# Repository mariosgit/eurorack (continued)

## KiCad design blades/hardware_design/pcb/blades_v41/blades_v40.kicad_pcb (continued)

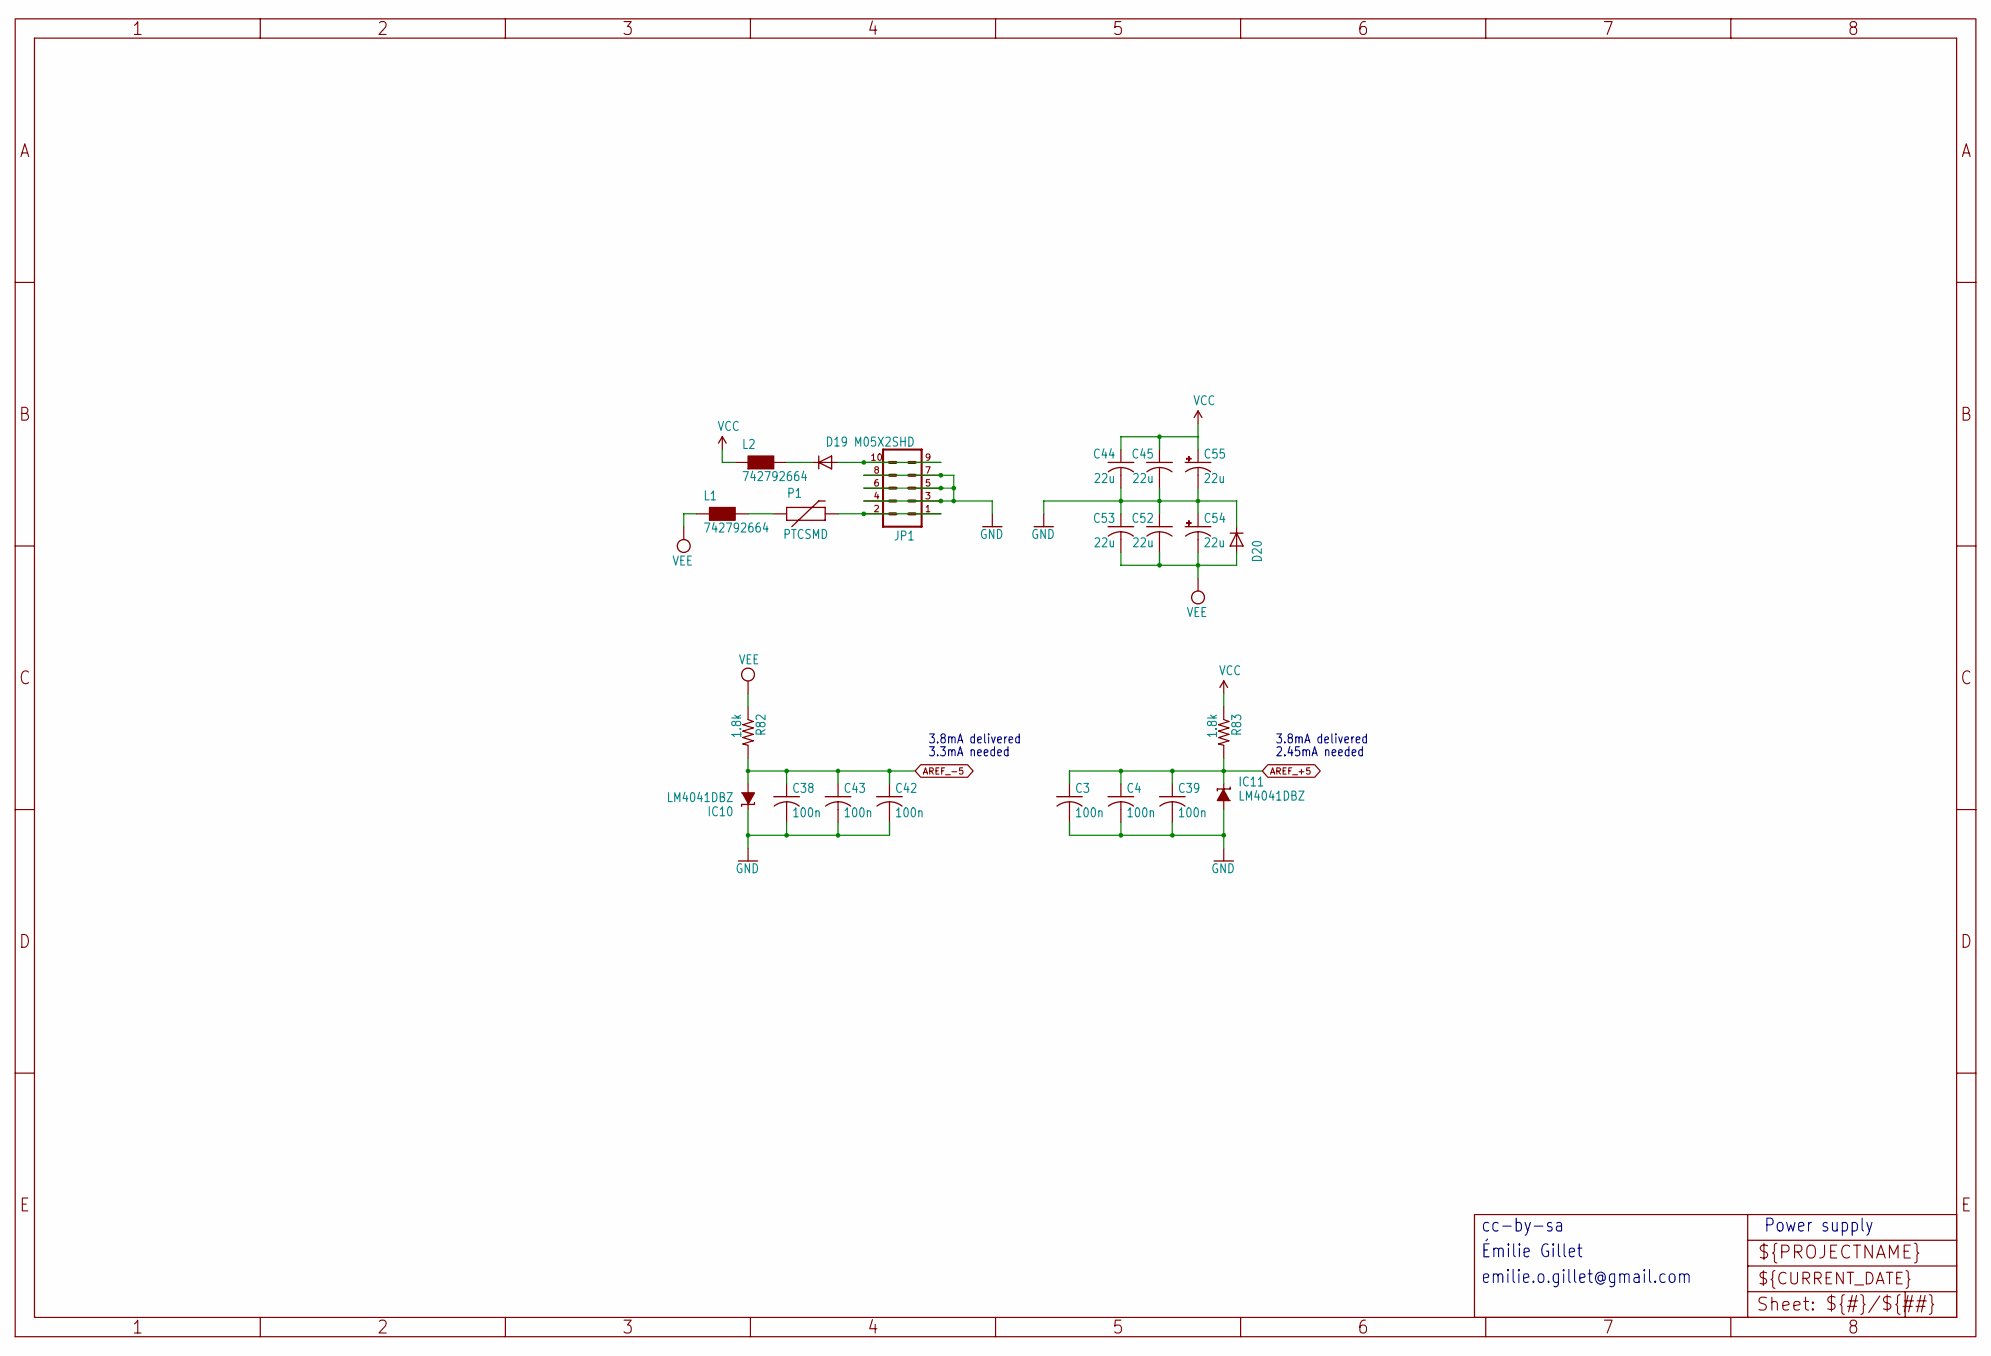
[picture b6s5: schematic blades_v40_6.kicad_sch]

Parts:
C3, C4, C38, C39, C42, C43: 100n; C0402
C44, C45, C52, C53: 22u; C1206
C54, C55: 22u; PANASONIC_B
D19, D20: 1N5819HW; SOD123
IC10, IC11: LM4041DBZ; DBZ_R-PDSO-G3
JP1: M05X2SHD; 2X5-SHROUDED
L1, L2: 742792664; 0603
P1: PTCSMD; PTC-1206
R82, R83: 1.8k; R0402

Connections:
AREF_+5: C3.1, C4.1, C39.1, IC11.1 (C), R83.2; also elsewhere on the board
AREF_-5: C38.1, C42.1, C43.1, IC10.2 (A), R82.2; also elsewhere on the board
GND: C3.2, C4.2, C38.2, C39.2, C42.2, C43.2, C44.2, C45.2, C52.1, C53.1, C54.+, C55.-, D20.C, IC10.1 (C), IC11.2 (A), JP1.3, JP1.4, JP1.5, JP1.6, JP1.7, JP1.8; also elsewhere on the board
unnamed: D19.A, JP1.9, JP1.10
unnamed: D19.C, L2.2
unnamed: JP1.1, JP1.2, P1.2
unnamed: L1.2, P1.1
VCC: C44.1, C45.1, C55.+, L2.1, R83.1; also elsewhere on the board
VEE: C52.2, C53.2, C54.-, D20.A, L1.1, R82.1; also elsewhere on the board

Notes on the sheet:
2.45mA needed
cc-by-sa
emilie.o.gillet@gmail.com
Émilie Gillet
3.8mA delivered
Power supply
3.3mA needed

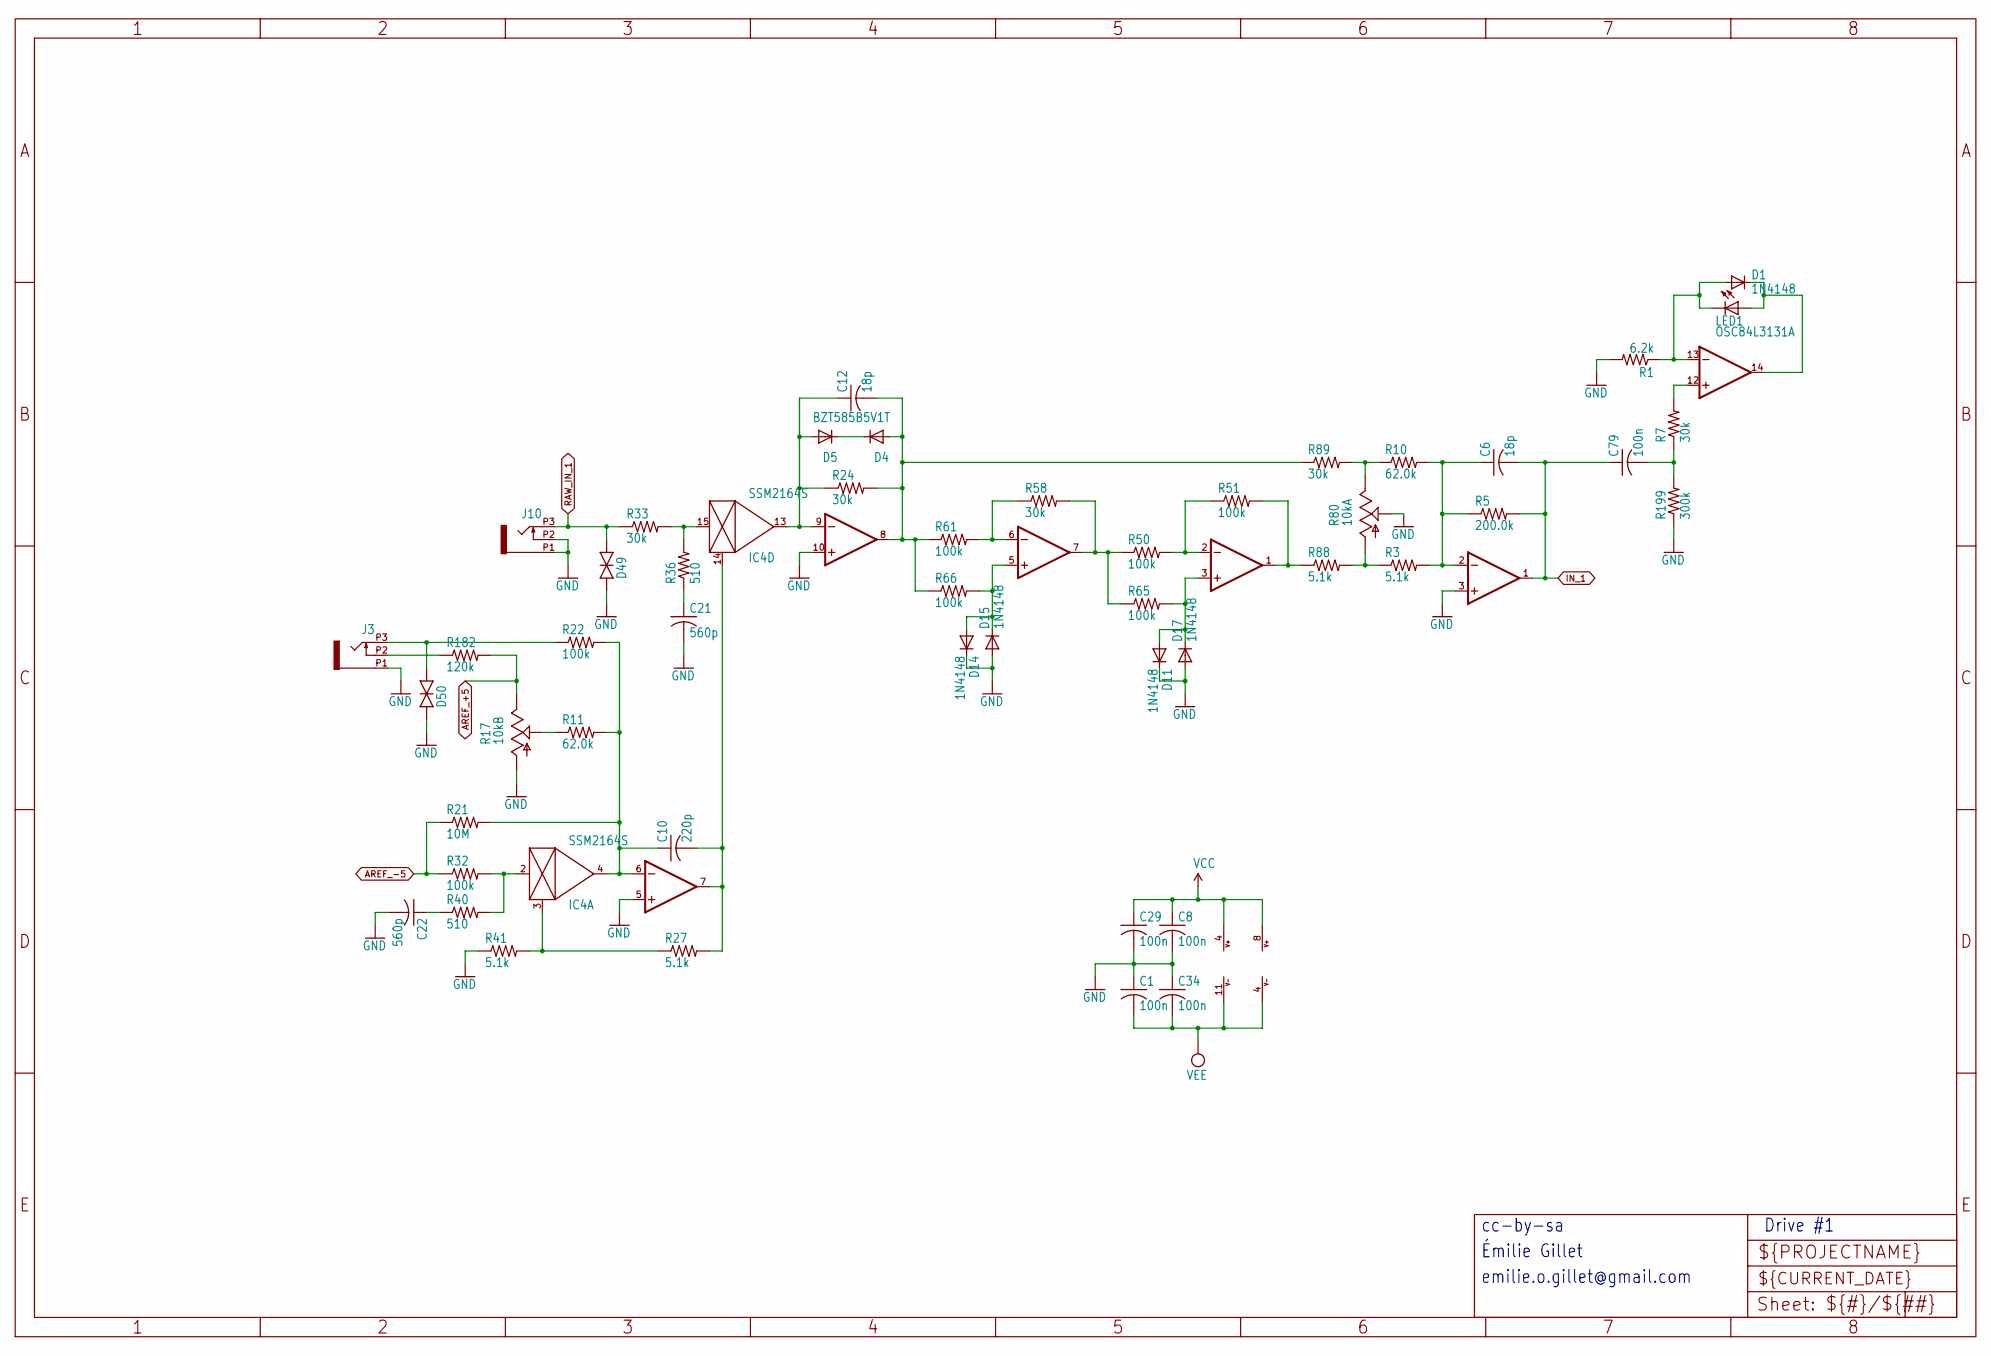
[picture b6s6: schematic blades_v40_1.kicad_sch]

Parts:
C1, C8, C29, C34, C79: 100n; C0402
C6, C12: 18p; C0402
C10: 220p; C0402
C21, C22: 560p; C0402
D1, D11, D14, D15, D17: 1N4148; SOD523
D4, D5: BZT585B5V1T; SOD523
D49, D50: TVS; 0603
IC2: OPA1679PW; TSSOP14_065
IC4: SSM2164S; SOIC16N
IC6: OPA1678DGK; VSSOP8
J3, J10: PJ301_THONKICONNTME; WQP_PJ_301M_TME
LED1: OSC84L3131A; LED3MM
R1: 6.2k; R0402
R3, R27, R41, R88: 5.1k; R0402
R5: 200.0k; R0402
R7, R24, R33, R58, R89: 30k; R0402
R10, R11: 62.0k; R0402
R17: 10kB; ALPS_POT_VERTICAL_PS
R21: 10M; R0402
R22, R32, R50, R51, R61, R65, R66: 100k; R0402
R36, R40: 510; R0402
R80: 10kA; ALPS_POT_NARROW
R182: 120k; R0402
R199: 300k; R0402

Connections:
AREF_+5: R17.P$1 (E), R182.2; also elsewhere on the board
AREF_-5: R21.1, R32.1; also elsewhere on the board
GND: C1.1, C8.2, C21.2, C22.2, C29.2, C34.1, D11.C, D14.C, D15.A, D17.A, D49.1 (A), D50.1 (A), IC2.3 (+IN), IC2.5 (+IN), IC2.10 (+IN), J3.P1 (1), J10.P1 (1), J10.P2 (2), R1.2, R17.P$3 (A), R41.1, R80.P$2 (S), R199.1; also elsewhere on the board
IN_1: C6.2, C79.1, IC2.1 (OUT), R5.2; also elsewhere on the board
unnamed: C21.1, R36.1
unnamed: C22.1, R40.1
unnamed: C79.2, R7.1, R199.2
unnamed: D4.C, D5.C
unnamed: D50.2 (C), J3.P3 (3), R22.1
unnamed: C6.1, IC2.2 (-IN), R3.2, R5.1, R10.2
unnamed: C10.1, IC2.6 (-IN), IC4.4 (OUT), R11.2, R21.2, R22.2
unnamed: C10.2, IC2.7 (OUT), IC4.14 (CTRL), R27.2
unnamed: C12.1, D5.A, IC2.9 (-IN), IC4.13 (OUT), R24.1
unnamed: C12.2, D4.A, IC2.8 (OUT), R24.2, R61.1, R66.1, R89.1
unnamed: IC2.12 (+IN), R7.2
unnamed: D1.A, IC2.13 (-IN), LED1.K (C), R1.1
unnamed: D1.C, IC2.14 (OUT), LED1.A
unnamed: IC4.3 (CTRL), R27.1, R41.2
unnamed: IC4.2 (IN), R32.2, R40.2
unnamed: IC4.15 (IN), R33.2, R36.2
unnamed: D11.A, D17.C, IC6.3 (+IN), R65.2
unnamed: IC6.2 (-IN), R50.2, R51.1
unnamed: IC6.1 (OUT), R51.2, R88.1
unnamed: D14.A, D15.C, IC6.5 (+IN), R66.2
unnamed: IC6.6 (-IN), R58.1, R61.2
unnamed: IC6.7 (OUT), R50.1, R58.2, R65.1
unnamed: J3.P2 (2), R182.1
unnamed: R11.1, R17.P$2 (S)
unnamed: R3.1, R80.P$3 (A), R88.2
unnamed: R10.1, R80.P$1 (E), R89.2
RAW_IN_1: D49.2 (C), J10.P3 (3), R33.1; also elsewhere on the board
VCC: C8.1, C29.1, IC2.4 (V+), IC6.8 (V+); also elsewhere on the board
VEE: C1.2, C34.2, IC2.11 (V-), IC6.4 (V-); also elsewhere on the board

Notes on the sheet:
emilie.o.gillet@gmail.com
cc-by-sa
Émilie Gillet
Drive #1

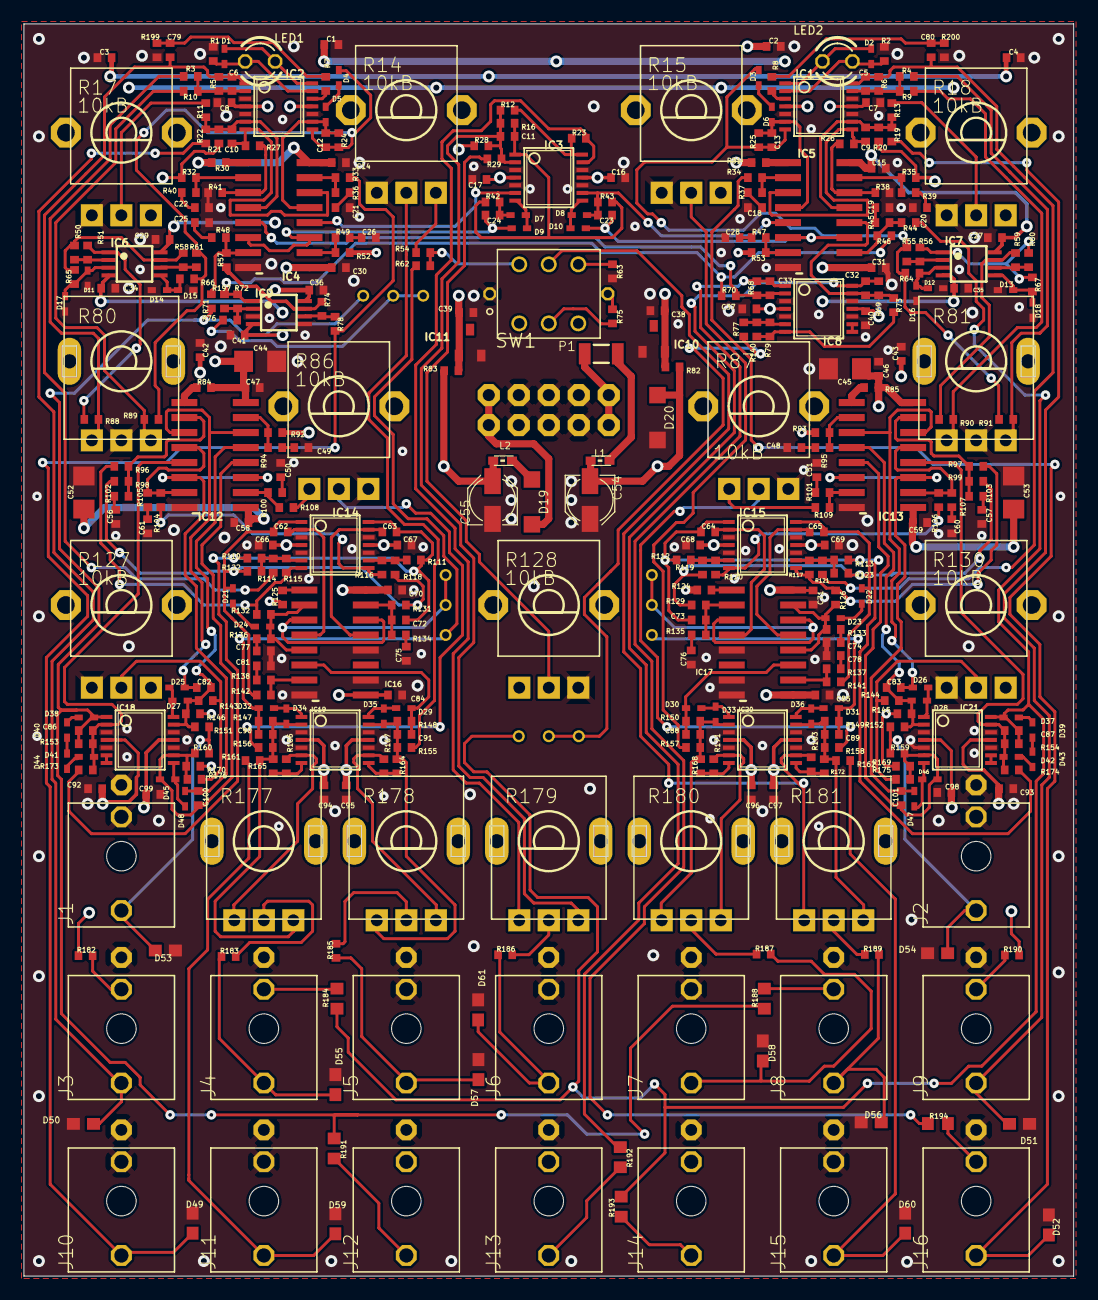
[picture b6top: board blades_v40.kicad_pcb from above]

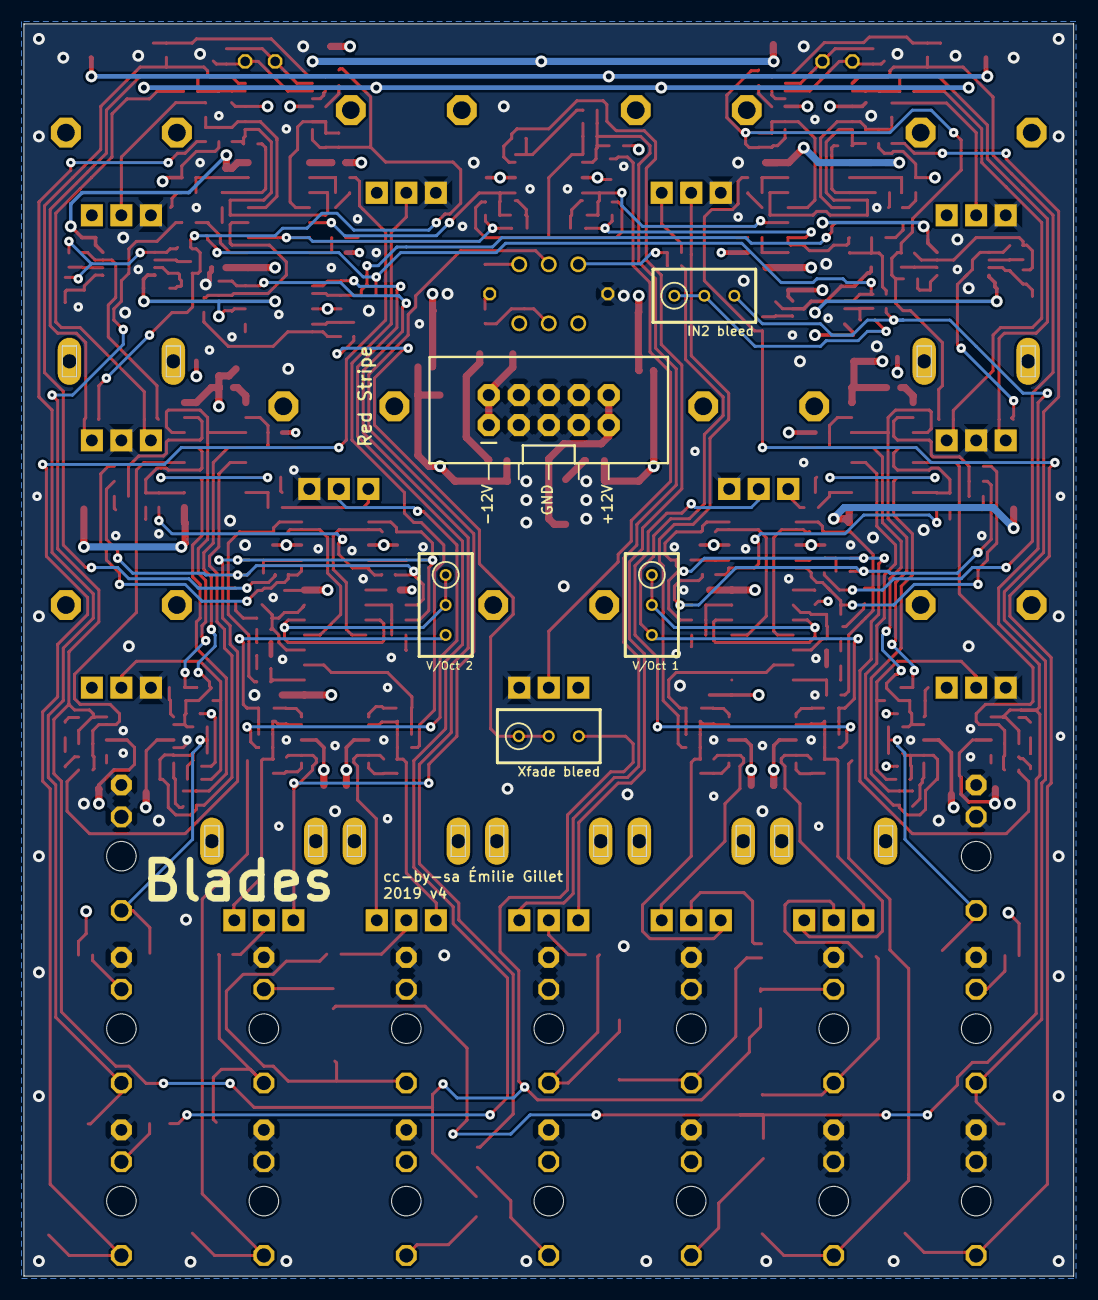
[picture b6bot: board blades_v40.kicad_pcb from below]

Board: 4 copper layers, 88.9 x 106.0 mm, 406 parts (5 on the bottom side), 225 nets.

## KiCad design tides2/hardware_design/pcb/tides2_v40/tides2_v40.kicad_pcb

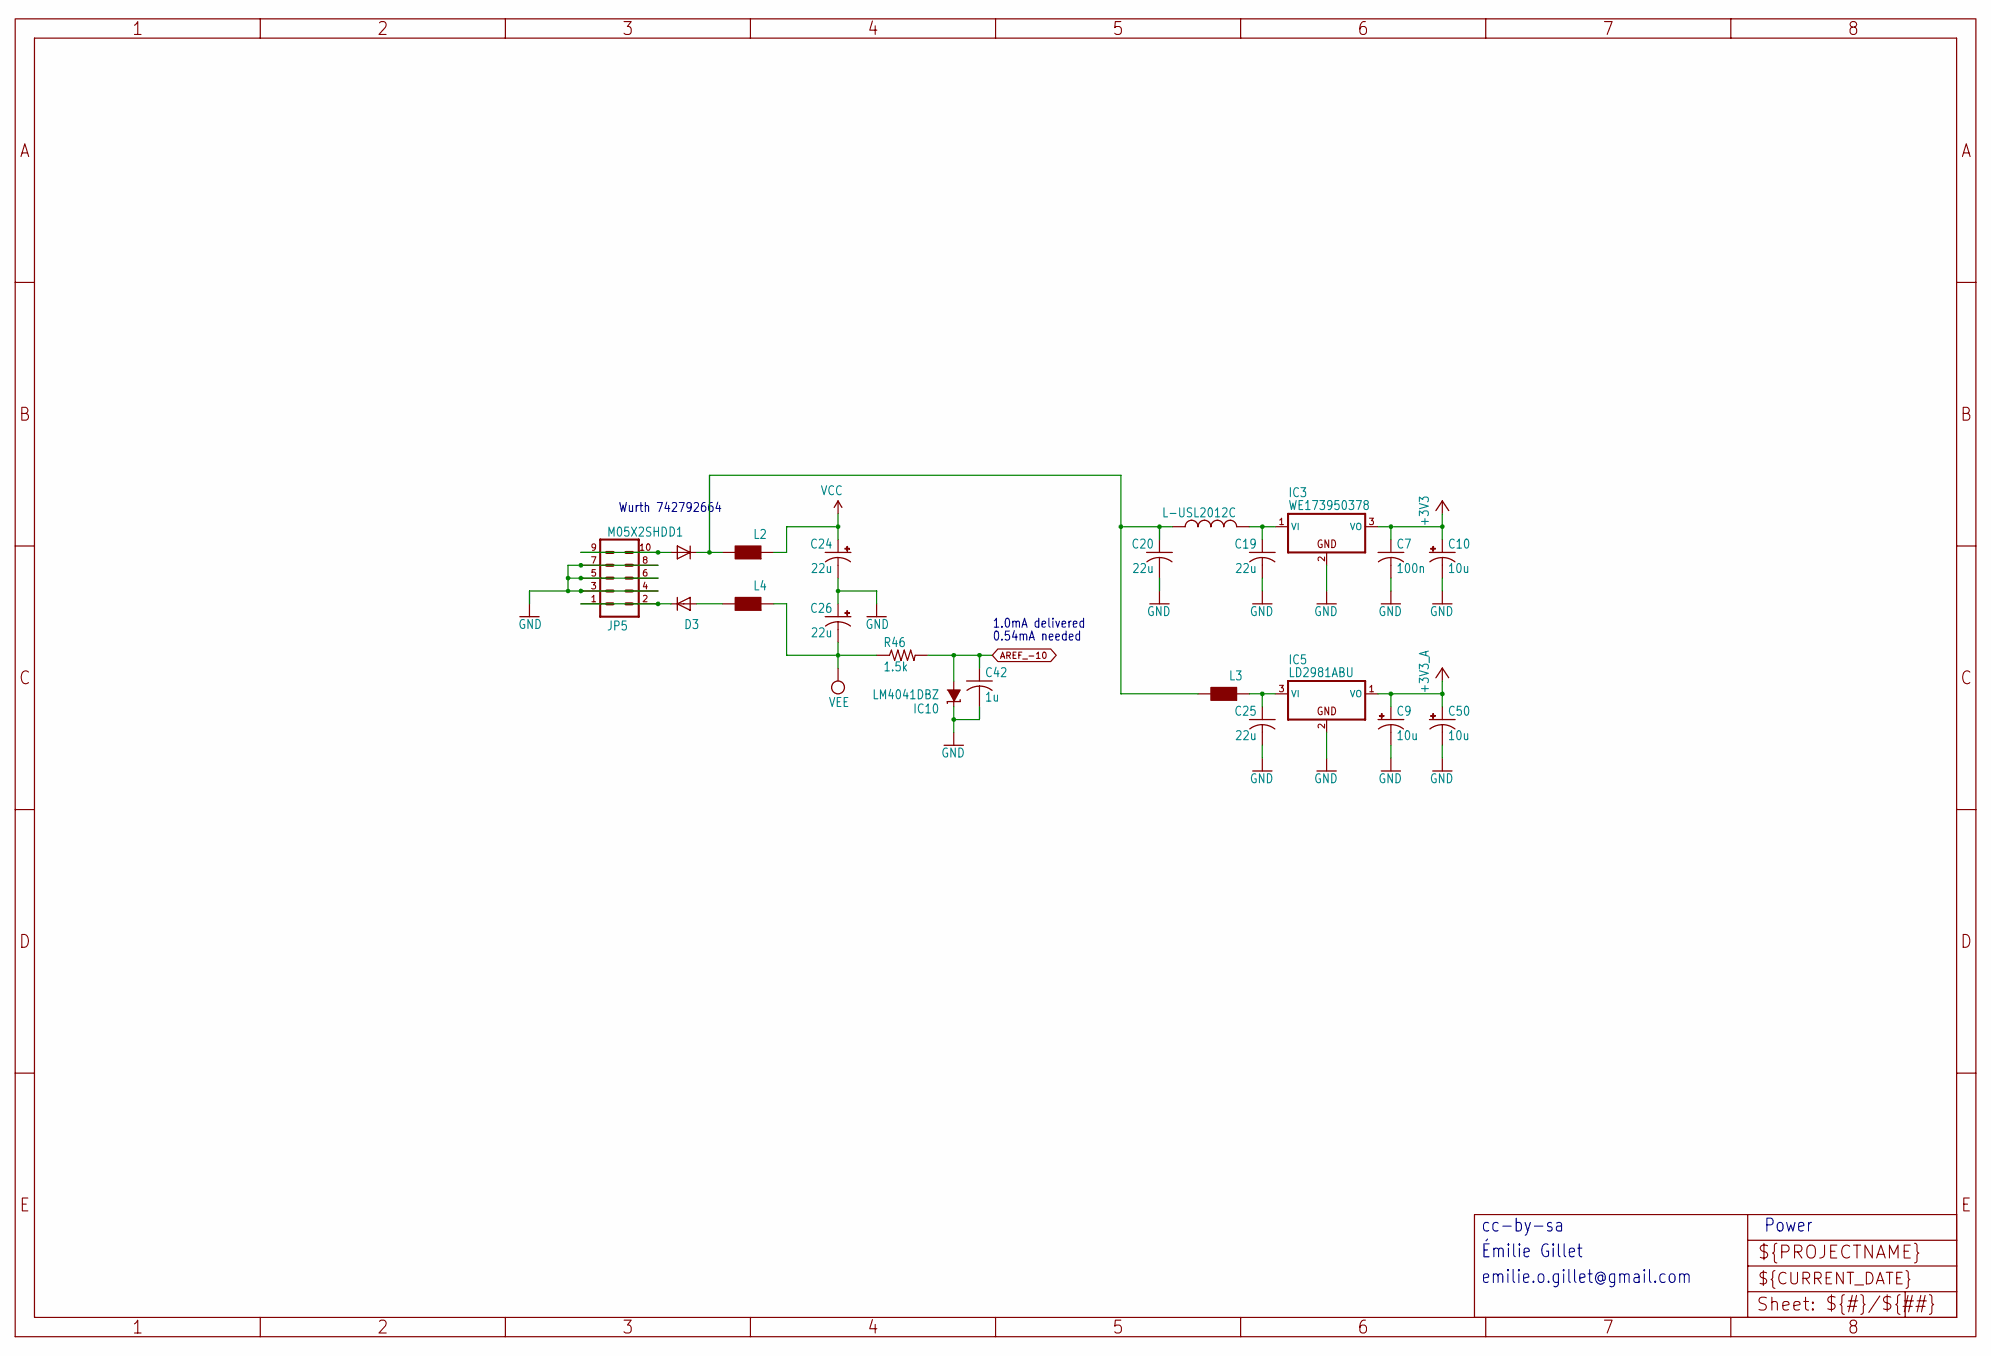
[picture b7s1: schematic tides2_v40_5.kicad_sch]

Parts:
C7: 100n; C0402
C9, C10, C50: 10u; PANASONIC_A
C19, C20, C25: 22u; C1206
C24, C26: 22u; PANASONIC_B
C42: 1u; C0402
D1, D3: 1N5819HW; SOD123
IC3: WE173950378; WE78
IC5: LD2981ABU; SOT89
IC10: LM4041DBZ; DBZ_R-PDSO-G3
JP5: M05X2SHD; 2X5-SHROUDED
L1: L-USL2012C; L2012C
L2, L3, L4: WE-CBF_0603; 0603
R46: 1.5k; R0402

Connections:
+3V3: C7.1, C10.+, IC3.3 (VO); also elsewhere on the board
+3V3_A: C9.+, C50.+, IC5.1 (VO); also elsewhere on the board
AREF_-10: C42.1, IC10.2 (A), R46.2; also elsewhere on the board
GND: C7.2, C9.-, C10.-, C19.2, C20.2, C24.-, C25.2, C26.+, C42.2, C50.-, IC3.2 (GND), IC5.2 (GND), IC10.1 (C), JP5.3, JP5.4, JP5.5, JP5.6, JP5.7, JP5.8; also elsewhere on the board
unnamed: C20.1, D1.C, L1.1, L2.2, L3.2
unnamed: D1.A, JP5.9, JP5.10
unnamed: D3.A, L4.2
unnamed: D3.C, JP5.1, JP5.2
unnamed: C19.1, IC3.1 (VI), L1.2
unnamed: C25.1, IC5.3 (VI), L3.1
VCC: C24.+, L2.1; also elsewhere on the board
VEE: C26.-, L4.1, R46.1; also elsewhere on the board

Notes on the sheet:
1.0mA delivered
Wurth 742792664
0.54mA needed
cc-by-sa
emilie.o.gillet@gmail.com
Power
Émilie Gillet

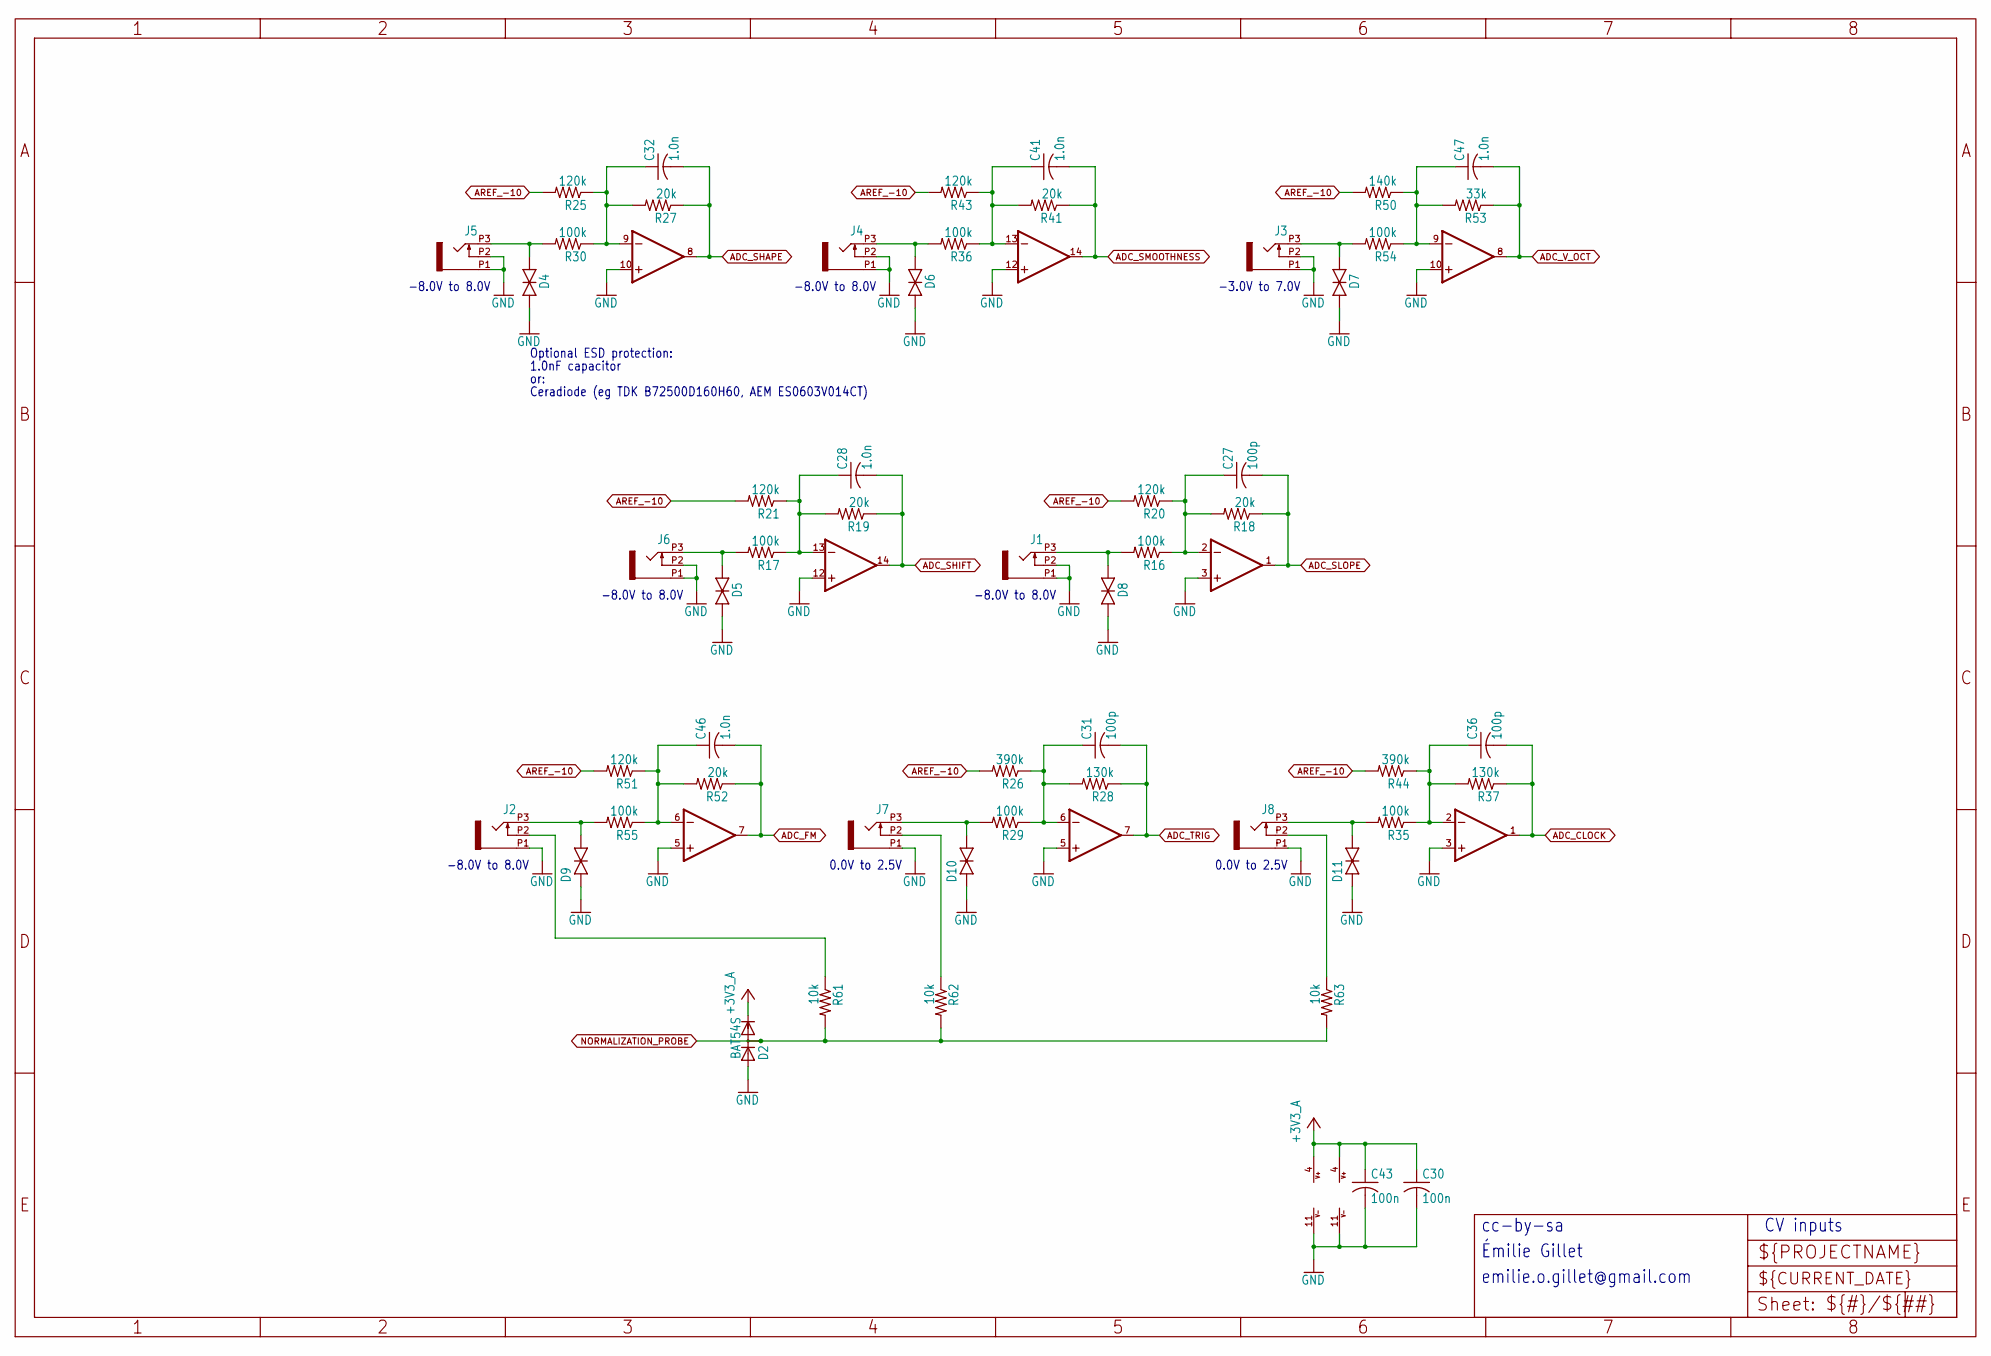
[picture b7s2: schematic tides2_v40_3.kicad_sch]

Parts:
C27, C31, C36: 100p; C0402
C28, C32, C41, C46, C47: 1.0n; C0402
C30, C43: 100n; C0402
D2: BAT54S; SOT23
D4, D5, D6, D7, D8, D9, D10, D11: TVS; 0603
IC6, IC7: TL074PW; TSSOP14_065
J1, J2, J3, J4, J5, J6, J7, J8: PJ301_THONKICONN6; WQP_PJ_301M6
R16, R17, R29, R30, R35, R36, R54, R55: 100k; R0402
R18, R19, R27, R41, R52: 20k; R0402
R20, R21, R25, R43, R51: 120k; R0402
R26, R44: 390k; R0402
R28, R37: 130k; R0402
R50: 140k; R0402
R53: 33k; R0402
R61, R62, R63: 10k; R0402

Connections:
+3V3_A: C30.1, C43.1, D2.2 (C), IC6.4 (V+), IC7.4 (V+); also elsewhere on the board
ADC_CLOCK: C36.2, IC7.1 (OUT), R37.1; also elsewhere on the board
ADC_FM: C46.2, IC7.7 (OUT), R52.1; also elsewhere on the board
ADC_SHAPE: C32.2, IC6.8 (OUT), R27.1; also elsewhere on the board
ADC_SHIFT: C28.2, IC6.14 (OUT), R19.1; also elsewhere on the board
ADC_SLOPE: C27.2, IC6.1 (OUT), R18.1; also elsewhere on the board
ADC_SMOOTHNESS: C41.2, IC7.14 (OUT), R41.1; also elsewhere on the board
ADC_TRIG: C31.2, IC6.7 (OUT), R28.1; also elsewhere on the board
ADC_V_OCT: C47.2, IC7.8 (OUT), R53.1; also elsewhere on the board
AREF_-10: R20.2, R21.2, R25.2, R26.2, R43.2, R44.2, R50.2, R51.2; also elsewhere on the board
GND: C30.2, C43.2, D2.1 (A), D4.1 (A), D5.1 (A), D6.1 (A), D7.1 (A), D8.1 (A), D9.1 (A), D10.1 (A), D11.1 (A), IC6.3 (+IN), IC6.5 (+IN), IC6.10 (+IN), IC6.11 (V-), IC6.12 (+IN), IC7.3 (+IN), IC7.5 (+IN), IC7.10 (+IN), IC7.11 (V-), IC7.12 (+IN), J1.P1 (1), J1.P2 (2), J2.P1 (1), J3.P1 (1), J3.P2 (2), J4.P1 (1), J4.P2 (2), J5.P1 (1), J5.P2 (2), J6.P1 (1), J6.P2 (2), J7.P1 (1), J8.P1 (1); also elsewhere on the board
NORMALIZATION_PROBE: D2.3 (AC), R61.2, R62.2, R63.2; also elsewhere on the board
unnamed: D4.2 (C), J5.P3 (3), R30.2
unnamed: D5.2 (C), J6.P3 (3), R17.2
unnamed: D6.2 (C), J4.P3 (3), R36.2
unnamed: D7.2 (C), J3.P3 (3), R54.2
unnamed: D8.2 (C), J1.P3 (3), R16.2
unnamed: D9.2 (C), J2.P3 (3), R55.2
unnamed: D10.2 (C), J7.P3 (3), R29.2
unnamed: D11.2 (C), J8.P3 (3), R35.2
unnamed: C27.1, IC6.2 (-IN), R16.1, R18.2, R20.1
unnamed: C31.1, IC6.6 (-IN), R26.1, R28.2, R29.1
unnamed: C32.1, IC6.9 (-IN), R25.1, R27.2, R30.1
unnamed: C28.1, IC6.13 (-IN), R17.1, R19.2, R21.1
unnamed: C36.1, IC7.2 (-IN), R35.1, R37.2, R44.1
unnamed: C46.1, IC7.6 (-IN), R51.1, R52.2, R55.1
unnamed: C47.1, IC7.9 (-IN), R50.1, R53.2, R54.1
unnamed: C41.1, IC7.13 (-IN), R36.1, R41.2, R43.1
unnamed: J2.P2 (2), R61.1
unnamed: J7.P2 (2), R62.1
unnamed: J8.P2 (2), R63.1

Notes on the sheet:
or:
CV inputs
0.0V to 2.5V
Émilie Gillet
1.0nF capacitor
-8.0V to 8.0V
-3.0V to 7.0V
cc-by-sa
emilie.o.gillet@gmail.com
Ceradiode (eg TDK B72500D160H60, AEM ES0603V014CT)
Optional ESD protection:

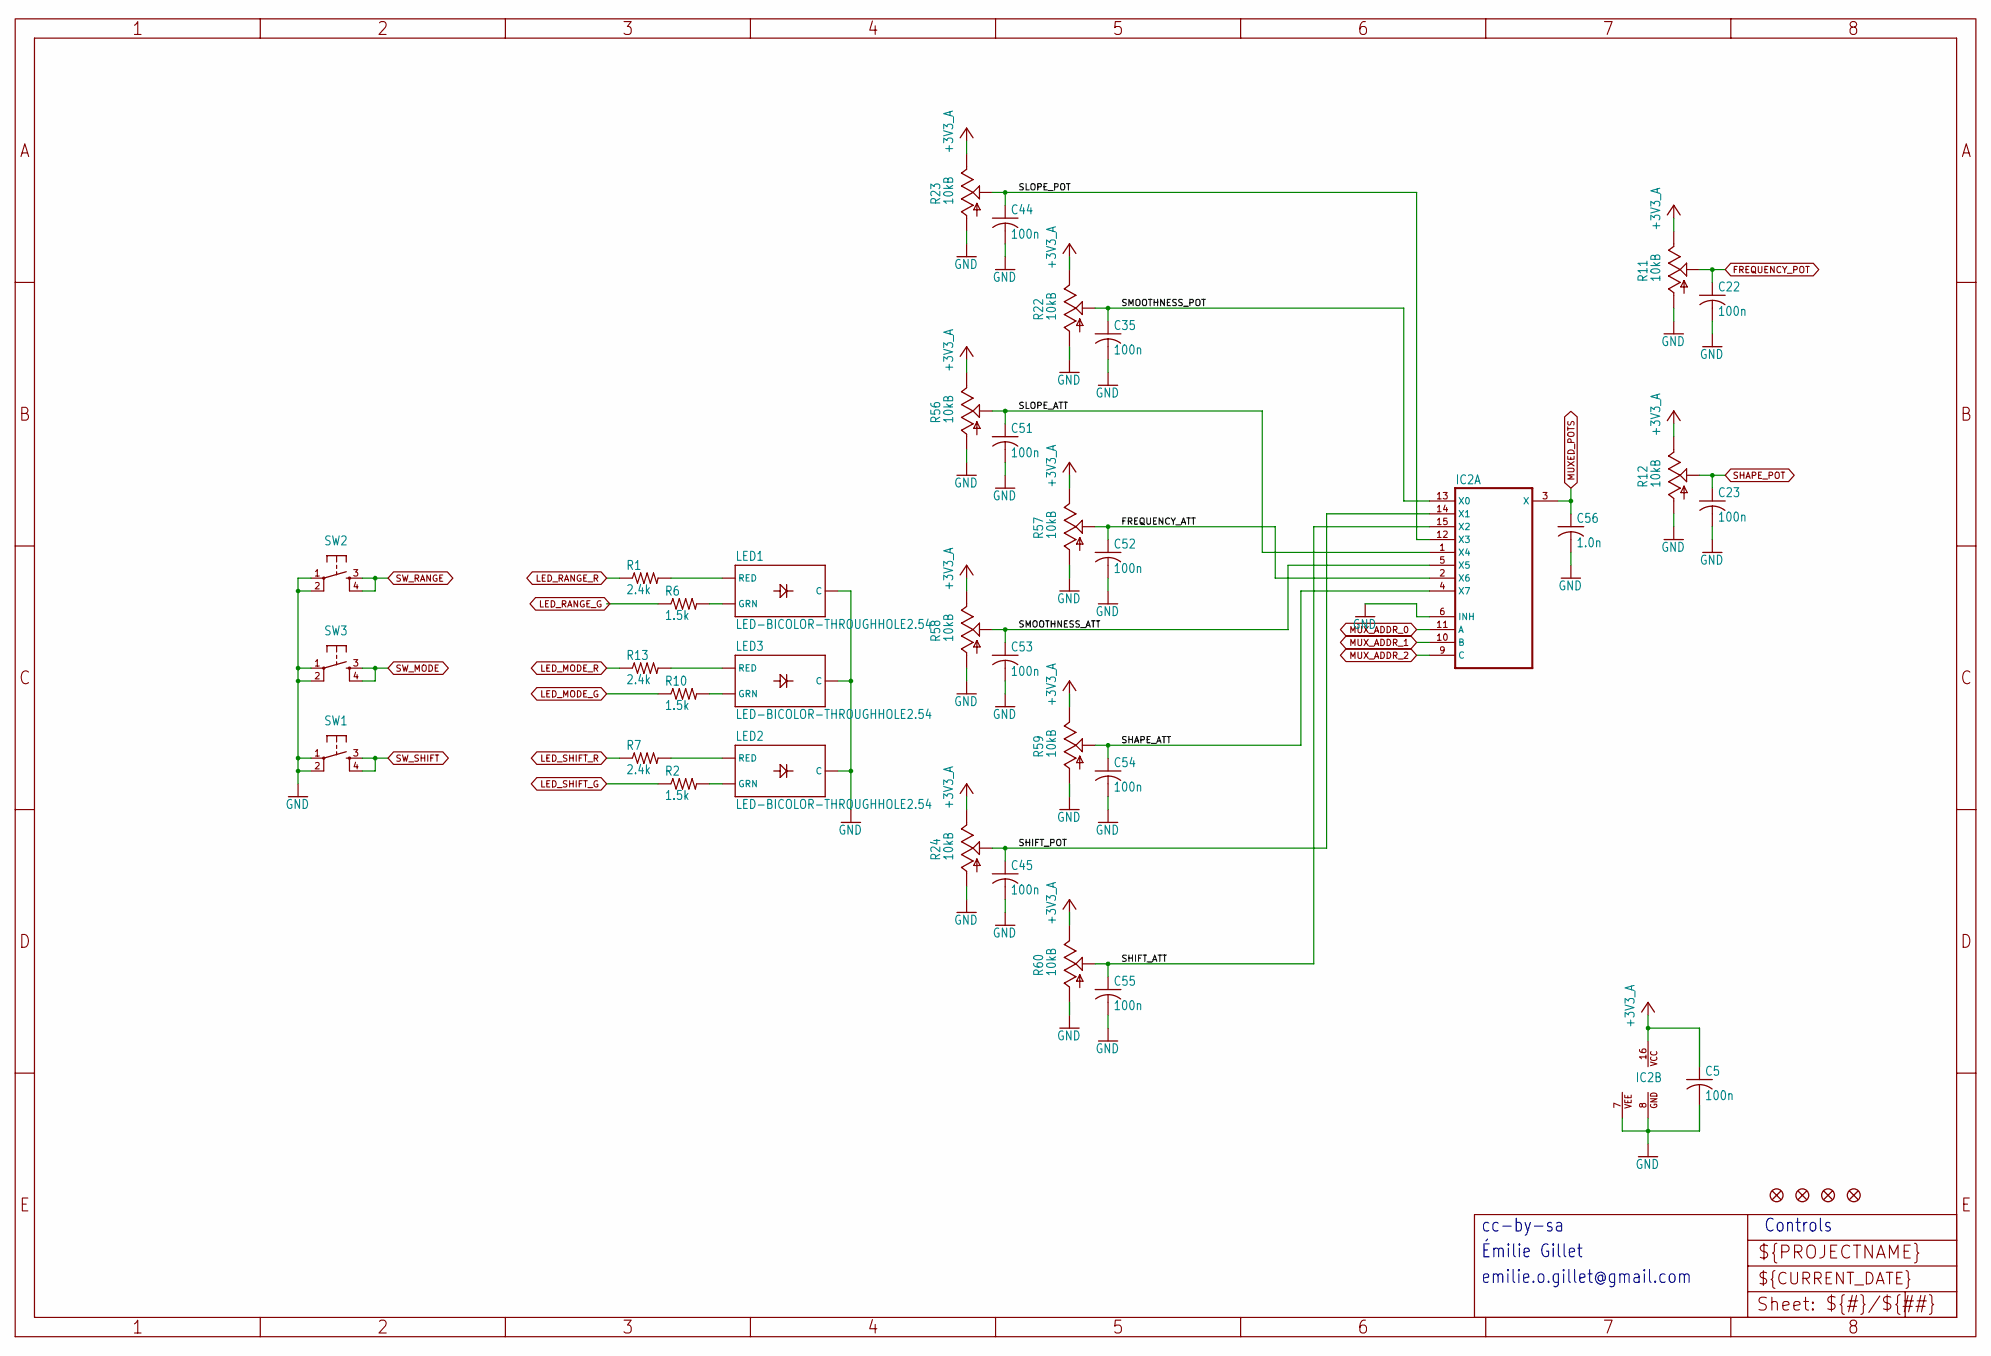
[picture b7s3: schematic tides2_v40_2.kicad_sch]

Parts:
C5, C22, C23, C35, C44, C45, C51, C52, C53, C54, C55: 100n; C0402
C56: 1.0n; C0402
IC2: 4051PW; TSSOP16_065
JP1, JP2, JP3, JP4: FIDUCIAL1X2; FIDUCIAL-1X2
LED1, LED2, LED3: LED-BICOLOR-THROUGHHOLE2.54; LED-BICOLOR-THROUGHHOLE-2.54
R1, R7, R13: 2.4k; R0402
R2, R6, R10: 1.5k; R0402
R11, R12, R22, R23, R24: 10kB; ALPS_POT_VERTICAL_PS
R56, R57, R58, R59, R60: 10kB; ALPS_POT_VERTICAL
SW1, SW2, SW3: TAC_SWITCHPTH; TACTILE-PTH

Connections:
+3V3_A: C5.1, IC2.16 (VCC), R11.P$1 (E), R12.P$1 (E), R22.P$1 (E), R23.P$1 (E), R24.P$1 (E), R56.P$1 (E), R57.P$1 (E), R58.P$1 (E), R59.P$1 (E), R60.P$1 (E); also elsewhere on the board
/tides2_v40_2/FREQUENCY_ATT: C52.1, IC2.2 (X6), R57.P$2 (S)
/tides2_v40_2/SHAPE_ATT: C54.1, IC2.4 (X7), R59.P$2 (S)
/tides2_v40_2/SHIFT_ATT: C55.1, IC2.15 (X2), R60.P$2 (S)
/tides2_v40_2/SHIFT_POT: C45.1, IC2.14 (X1), R24.P$2 (S)
/tides2_v40_2/SLOPE_ATT: C51.1, IC2.1 (X4), R56.P$2 (S)
/tides2_v40_2/SLOPE_POT: C44.1, IC2.12 (X3), R23.P$2 (S)
/tides2_v40_2/SMOOTHNESS_ATT: C53.1, IC2.5 (X5), R58.P$2 (S)
/tides2_v40_2/SMOOTHNESS_POT: C35.1, IC2.13 (X0), R22.P$2 (S)
FREQUENCY_POT: C22.1, R11.P$2 (S); also elsewhere on the board
GND: C5.2, C22.2, C23.2, C35.2, C44.2, C45.2, C51.2, C52.2, C53.2, C54.2, C55.2, C56.2, IC2.6 (INH), IC2.7 (VEE), IC2.8 (GND), LED1.2 (C), LED2.2 (C), LED3.2 (C), R11.P$3 (A), R12.P$3 (A), R22.P$3 (A), R23.P$3 (A), R24.P$3 (A), R56.P$3 (A), R57.P$3 (A), R58.P$3 (A), R59.P$3 (A), R60.P$3 (A), SW1.1, SW1.2, SW2.1, SW2.2, SW3.1, SW3.2; also elsewhere on the board
LED_MODE_G: R10.1; also elsewhere on the board
LED_MODE_R: R13.1; also elsewhere on the board
LED_RANGE_G: R6.1; also elsewhere on the board
LED_RANGE_R: R1.1; also elsewhere on the board
LED_SHIFT_G: R2.1; also elsewhere on the board
LED_SHIFT_R: R7.1; also elsewhere on the board
MUXED_POTS: C56.1, IC2.3 (X); also elsewhere on the board
MUX_ADDR_0: IC2.11 (A); also elsewhere on the board
MUX_ADDR_1: IC2.10 (B); also elsewhere on the board
MUX_ADDR_2: IC2.9 (C); also elsewhere on the board
unnamed: LED1.1 (GRN), R6.2
unnamed: LED1.3 (RED), R1.2
unnamed: LED2.1 (GRN), R2.2
unnamed: LED2.3 (RED), R7.2
unnamed: LED3.1 (GRN), R10.2
unnamed: LED3.3 (RED), R13.2
SHAPE_POT: C23.1, R12.P$2 (S); also elsewhere on the board
SW_MODE: SW3.3, SW3.4; also elsewhere on the board
SW_RANGE: SW2.3, SW2.4; also elsewhere on the board
SW_SHIFT: SW1.3, SW1.4; also elsewhere on the board

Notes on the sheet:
Controls
emilie.o.gillet@gmail.com
cc-by-sa
Émilie Gillet
